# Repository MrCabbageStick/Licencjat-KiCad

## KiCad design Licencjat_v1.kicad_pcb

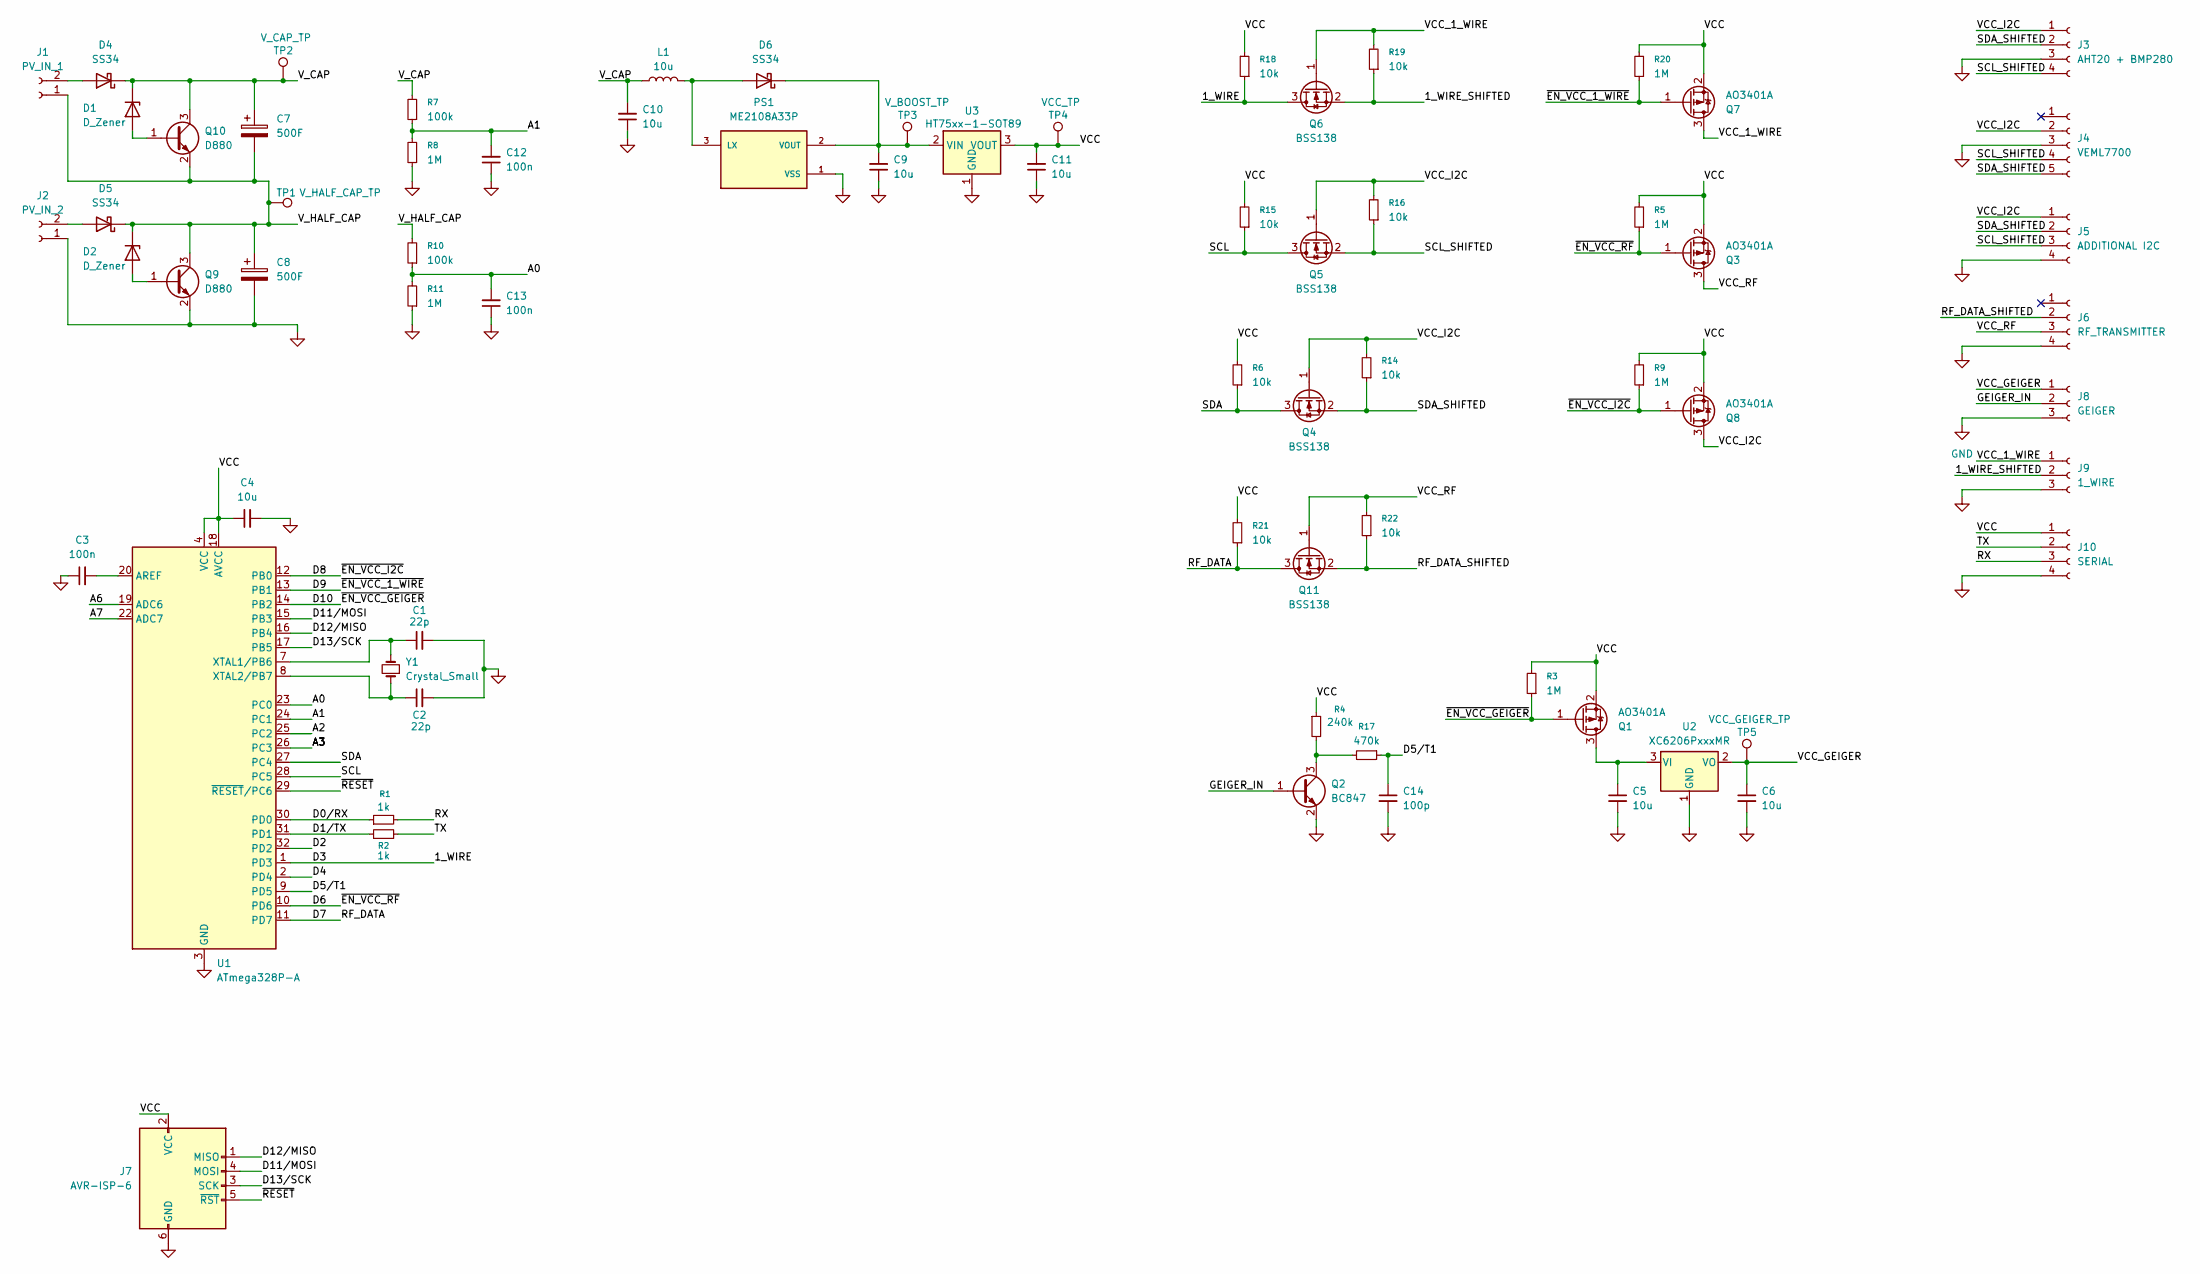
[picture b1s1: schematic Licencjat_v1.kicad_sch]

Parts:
C1, C2: 22p; C_1206_3216Metric
C3, C12, C13: 100n; C_1206_3216Metric
C4, C5, C6, C9, C10, C11: 10u; C_1206_3216Metric
C7, C8: 500F; Super Capacitor
C14: 100p; C_1206_3216Metric
D1, D2: D_Zener; D_MiniMELF
D4, D5, D6: SS34; D_SMA
J1: PV_IN_1; PinHeader_1x02_P2.54mm_Vertical
J2: PV_IN_2; PinHeader_1x02_P2.54mm_Vertical
J3: AHT20 + BMP280; ATH20 + BMP280
J4: VEML7700
J5: ADDITIONAL I2C; PinHeader_1x04_P2.54mm_Vertical
J6: RF_TRANSMITTER
J7: AVR-ISP-6; IDC-Header_2x03_P2.54mm_Vertical
J8: GEIGER; PinHeader_1x03_P2.54mm_Vertical
J9: 1_WIRE; PinHeader_1x03_P2.54mm_Vertical
J10: SERIAL; PinHeader_1x04_P2.54mm_Vertical
L1: 10u; IND_CD54_SUM
PS1: ME2108A33P; CONV_ME2108A33P; PARTREV V10.0
Q1, Q3, Q7, Q8: AO3401A; SOT-23
Q2: BC847; SOT-23
Q4, Q5, Q6, Q11: BSS138; SOT-23
Q9, Q10: D880; TO-220-3_Vertical+Radiator
R1, R2: 1k; R_1206_3216Metric
R3, R5, R8, R9, R11, R20: 1M; R_1206_3216Metric
R4: 240k; R_1206_3216Metric
R6, R14, R15, R16, R18, R19, R21, R22: 10k; R_1206_3216Metric
R7, R10: 100k; R_1206_3216Metric
R17: 470k; R_1206_3216Metric
TP1: V_HALF_CAP_TP; TestPoint_Pad_D2.0mm
TP2: V_CAP_TP; TestPoint_Pad_D2.0mm
TP3: V_BOOST_TP; TestPoint_Pad_D2.0mm
TP4: VCC_TP; TestPoint_Pad_D2.0mm
TP5: VCC_GEIGER_TP; TestPoint_Pad_D2.0mm
U1: ATmega328P-A; TQFP-32_7x7mm_P0.8mm
U2: XC6206PxxxMR; SOT-23-3
U3: HT75xx-1-SOT89; SOT-89-3
Y1: Crystal_Small; Crystal_SMD_HC49-SD

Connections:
/1_WIRE: Q6.3 (D), R18.1, U1.1 (PD3)
/1_WIRE_SHIFTED: J9.2, Q6.2 (S), R19.1
/A0: C13.2, R10.1, R11.2, U1.23 (PC0)
/A1: C12.2, R7.1, R8.2, U1.24 (PC1)
/A2: U1.25 (PC2)
/A3: U1.26 (PC3)
/A6: U1.19 (ADC6)
/A7: U1.22 (ADC7)
/D0/RX: R1.1, U1.30 (PD0)
/D1/TX: R2.1, U1.31 (PD1)
/D2: U1.32 (PD2)
/D4: U1.2 (PD4)
/D5/T1: C14.1, R17.1, U1.9 (PD5)
/D6: Q3.1 (G), R5.1, U1.10 (PD6)
/D7: Q11.3 (D), R21.1, U1.11 (PD7)
/D8: Q8.1 (G), R9.1, U1.12 (PB0)
/D9: Q7.1 (G), R20.1, U1.13 (PB1)
/D10: Q1.1 (G), R3.1, U1.14 (PB2)
/D11/MOSI: J7.4 (MOSI), U1.15 (PB3)
/D12/MISO: J7.1 (MISO), U1.16 (PB4)
/D13/SCK: J7.3 (SCK), U1.17 (PB5)
/GEIGER_IN: J8.2, Q2.1 (B)
/RF_DATA_SHIFTED: J6.2, Q11.2 (S), R22.1
/RX: J10.3, R1.2
/SCL: Q5.3 (D), R15.1, U1.28 (PC5)
/SCL_SHIFTED: J3.4, J4.4, J5.3, Q5.2 (S), R16.1
/SDA: Q4.3 (D), R6.1, U1.27 (PC4)
/SDA_SHIFTED: J3.2, J4.5, J5.2, Q4.2 (S), R14.1
/TX: J10.2, R2.2
/VCC: C4.1, C11.2, J7.2 (VCC), J10.1, Q1.2 (S), Q3.2 (S), Q7.2 (S), Q8.2 (S), R3.2, R4.1, R5.2, R6.2, R9.2, R15.2, R18.2, R20.2, R21.2, TP4.1, U1.4 (VCC), U1.6 (VCC), U1.18 (AVCC), U3.3 (VOUT)
/VCC_1_WIRE: J9.1, Q6.1 (G), Q7.3 (D), R19.2
/VCC_GEIGER: C6.1, J8.1, TP5.1, U2.2 (VO)
/VCC_I2C: J3.1, J4.2, J5.1, Q4.1 (G), Q5.1 (G), Q8.3 (D), R14.2, R16.2
/VCC_RF: J6.3, Q3.3 (D), Q11.1 (G), R22.2
/V_CAP: C7.1, C10.2, D1.1 (K), D4.1 (K), L1.1, Q10.3 (C), R7.2, TP2.1
/V_HALF_CAP: C7.2, C8.1, D2.1 (K), D5.1 (K), J1.1, Q9.3 (C), Q10.2 (E), R10.2, TP1.1
/~RESET: J7.5 (~RST), U1.29 (~RESET/PC6)
GND: C1.2, C2.2, C3.1, C4.2, C5.2, C6.2, C8.2, C9.1, C10.1, C11.1, C12.1, C13.1, C14.2, J2.1, J3.3, J4.3, J5.4, J6.4, J7.6 (GND), J8.3, J9.3, J10.4, PS1.1 (VSS), Q2.2 (E), Q9.2 (E), R8.1, R11.1, U1.3 (GND), U1.5 (GND), U1.21 (GND), U2.1 (GND), U3.1 (GND)
unnamed: D1.2 (A), Q10.1 (B)
unnamed: D2.2 (A), Q9.1 (B)
unnamed: D4.2 (A), J1.2
unnamed: D5.2 (A), J2.2
unnamed: D6.2 (A), L1.2, PS1.3 (LX)
unnamed: C9.2, D6.1 (K), PS1.2 (VOUT), TP3.1, U3.2 (VIN)
unnamed: C5.1, Q1.3 (D), U2.3 (VI)
unnamed: Q2.3 (C), R4.2, R17.2
unnamed: C3.2, U1.20 (AREF)
unnamed: C1.1, U1.7 (XTAL1/PB6), Y1.2
unnamed: C2.1, U1.8 (XTAL2/PB7), Y1.1

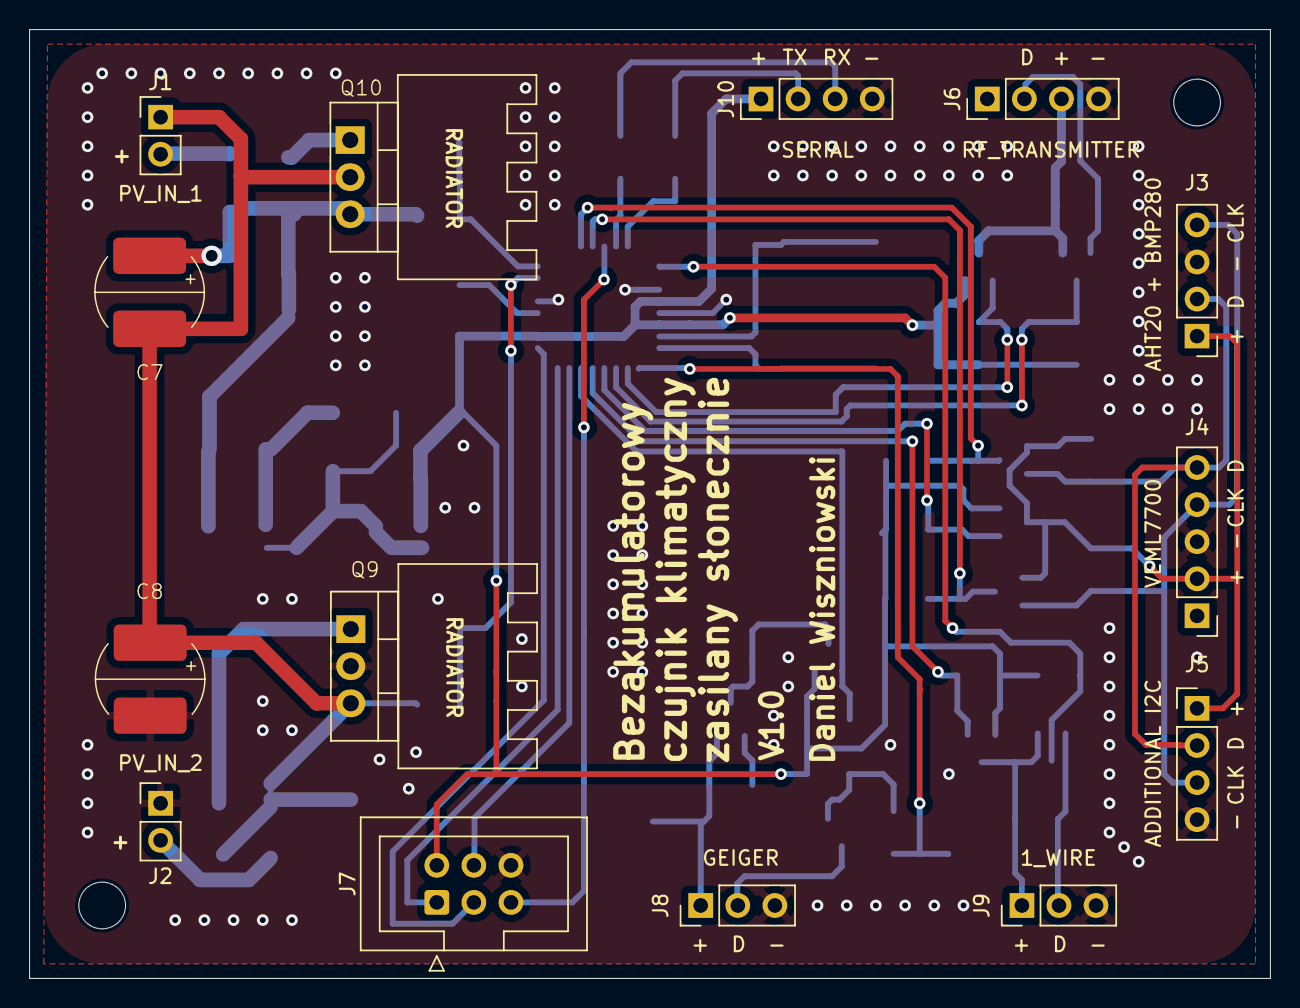
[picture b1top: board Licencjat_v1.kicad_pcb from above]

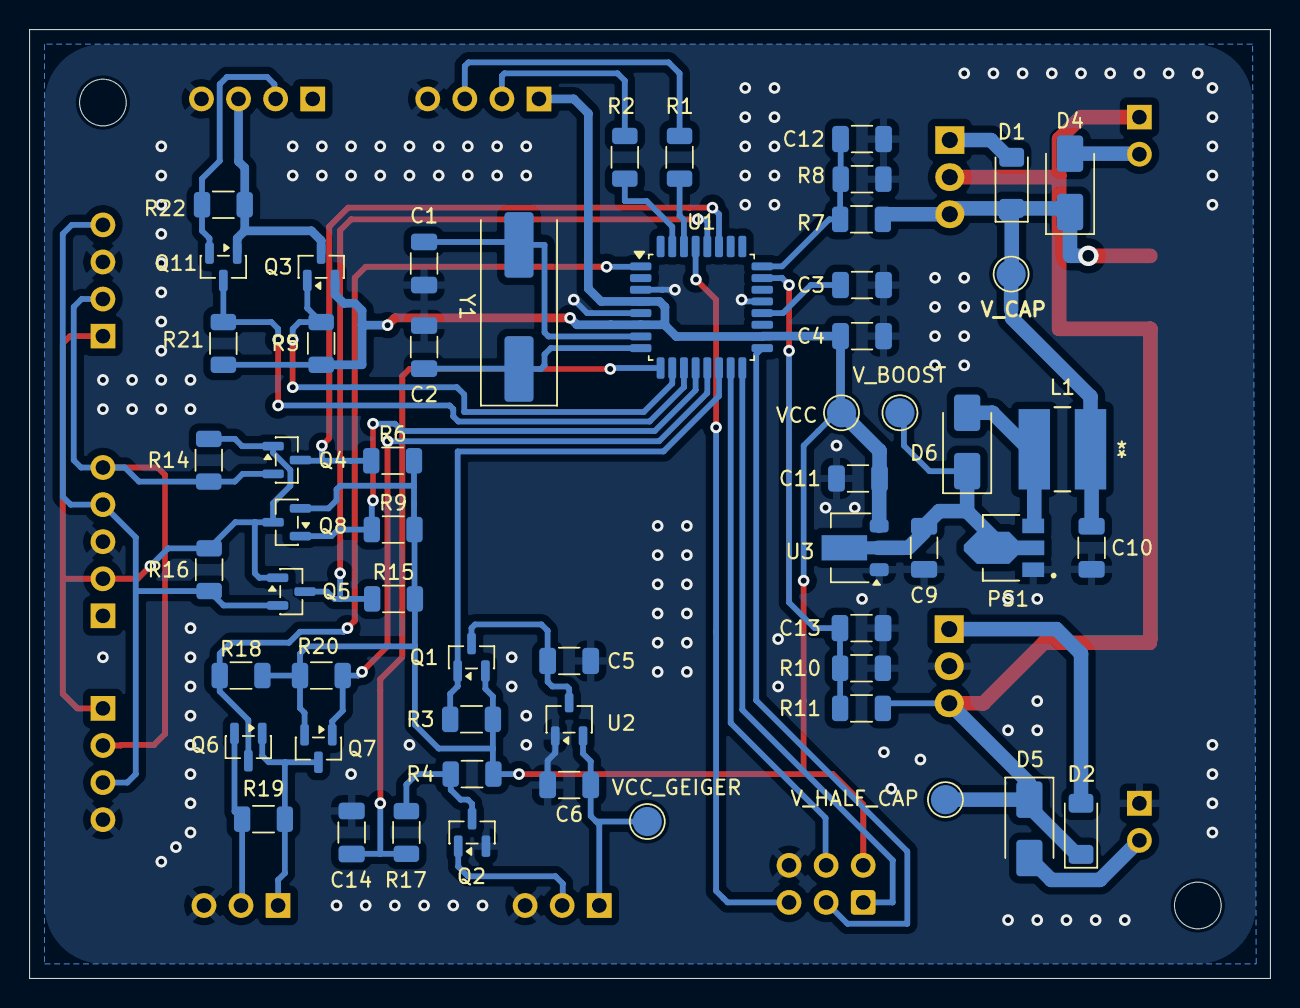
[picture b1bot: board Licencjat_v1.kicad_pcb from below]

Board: 2 copper layers, 85.0 x 65.0 mm, 71 parts (57 on the bottom side), 43 nets.

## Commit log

2025-12-09 Add i2c devices power management section
2025-12-09 Add shcematic PDF
2026-01-08 Add i2c level shifters
2026-01-10 Set pull-up resistors to 10k
2026-01-18 Add footprints
2026-01-18 Add 1Wire, RF Level SHifter and better footprints
2026-01-18 Start placing components
2026-01-18 Component placing continues
2026-01-22 Component placing
2026-01-23 Elements placed
2026-01-24 Tracks placed
2026-01-24 Labels placed
2026-01-24 More labels
2026-01-24 Whetever happened here
2026-01-24 Larger tracks in power section
2026-01-24 Add caption
2026-01-24 Generate production files
2026-02-14 Adjust values
